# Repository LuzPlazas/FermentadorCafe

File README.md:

# FermentadorCafe
Códigos asociados al monitor de fermentación de café
-----------

DESARROLLO DE UN SISTEMA PARA EL MONITOREO INTELIGENTE DEL PROCESO DE FERMENTACIÓN DEL CAFÉ 

LUZ ADRIANA PLAZAS PEMBERTHY
CÓDIGO 2190651

UNIVERSIDAD AUTÓNOMA DE OCCIDENTE
2022

------------------------------
Código generado en el desarrollo de un sistema de monitoreo inteligente del proceso de fermentación del café para facilitarle al caficultor la producción de diferentes perfiles de café.

* Se encuentra el firmware para Arduino para la lectura y procesamiento de sensores.
* Se encuentra el software para Raspberry desarrollado en python para almacenamiento y análisis de datos.
* Se encuentran los códigos para entrenamiento de los modelos de aprendizaje automático y los dataset asociados en formato csv.

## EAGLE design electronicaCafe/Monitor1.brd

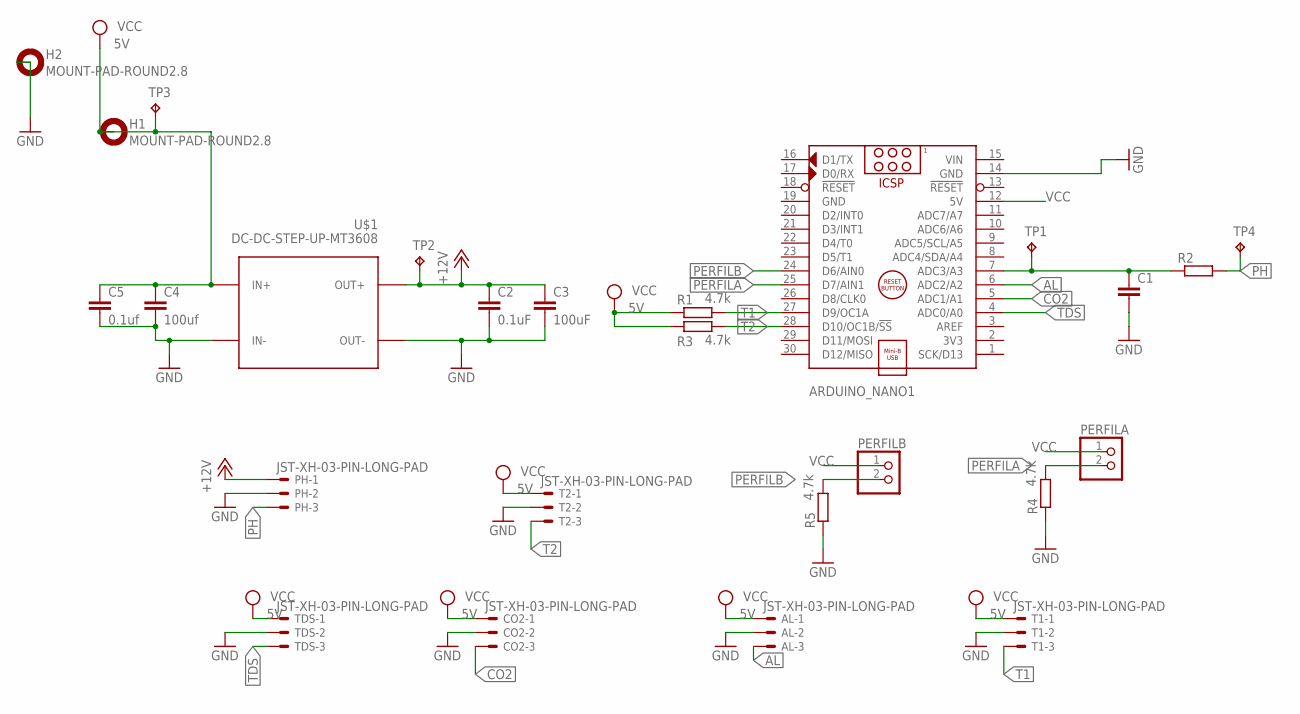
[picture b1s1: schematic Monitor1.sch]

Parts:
AL: JST-XH-03-PIN-LONG-PAD; JST-XH-03-PACKAGE-LONG-PAD
ARDUINO_NANO1: ARDUINO_NANO
C1: C-EU050-030X075; C050-030X075
C2: 0.1uF; C050-030X075
C3: 100uF; C050-045X075
C4: 100uf; C050-045X075
C5: 0.1uf; C050-030X075
CO2: JST-XH-03-PIN-LONG-PAD; JST-XH-03-PACKAGE-LONG-PAD
H1, H2: MOUNT-PAD-ROUND2.8; 2,8-PAD
PERFILA: PINHD-1X2; 1X02
PERFILB: PINHD-1X2; 1X02
PH: JST-XH-03-PIN-LONG-PAD; JST-XH-03-PACKAGE-LONG-PAD
R1, R3, R4, R5: 4.7k; 0309/10
R2: R-EU_0309/10; 0309/10
T1, T2: JST-XH-03-PIN-LONG-PAD; JST-XH-03-PACKAGE-LONG-PAD
TDS: JST-XH-03-PIN-LONG-PAD; JST-XH-03-PACKAGE-LONG-PAD
TP1, TP2, TP3, TP4: TPPAD1-13; P1-13
U$1: DC-DC-STEP-UP-MT3608

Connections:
+12V: C2.1, C3.1, PH.1, TP2.TP, U$1.OUT+
AL: AL.3, ARDUINO_NANO1.6 (ADC2/A2)
CO2: ARDUINO_NANO1.5 (ADC1/A1), CO2.3
GND: AL.2, ARDUINO_NANO1.14 (GND), ARDUINO_NANO1.19 (GND), C1.2, C2.2, C3.2, C4.2, C5.2, CO2.2, H2.B2,8, PH.2, R4.1, R5.1, T1.2, T2.2, TDS.2, U$1.IN-, U$1.OUT-
unnamed: ARDUINO_NANO1.7 (ADC3/A3), C1.1, R2.1, TP1.TP
PERFILA: ARDUINO_NANO1.25 (D7/AIN1), PERFILA.2, R4.2
PERFILB: ARDUINO_NANO1.24 (D6/AIN0), PERFILB.2, R5.2
PH: PH.3, R2.2, TP4.TP
T1: ARDUINO_NANO1.27 (D9/OC1A), R1.2, T1.3
T2: ARDUINO_NANO1.28 (D10/OC1B/!SS), R3.2, T2.3
TDS: ARDUINO_NANO1.4 (ADC0/A0), TDS.3
VCC: AL.1, ARDUINO_NANO1.12 (5V), C4.1, C5.1, CO2.1, H1.B2,8, PERFILA.1, PERFILB.1, R1.1, R3.1, T1.1, T2.1, TDS.1, TP3.TP, U$1.IN+
VIN: ARDUINO_NANO1.15 (VIN)

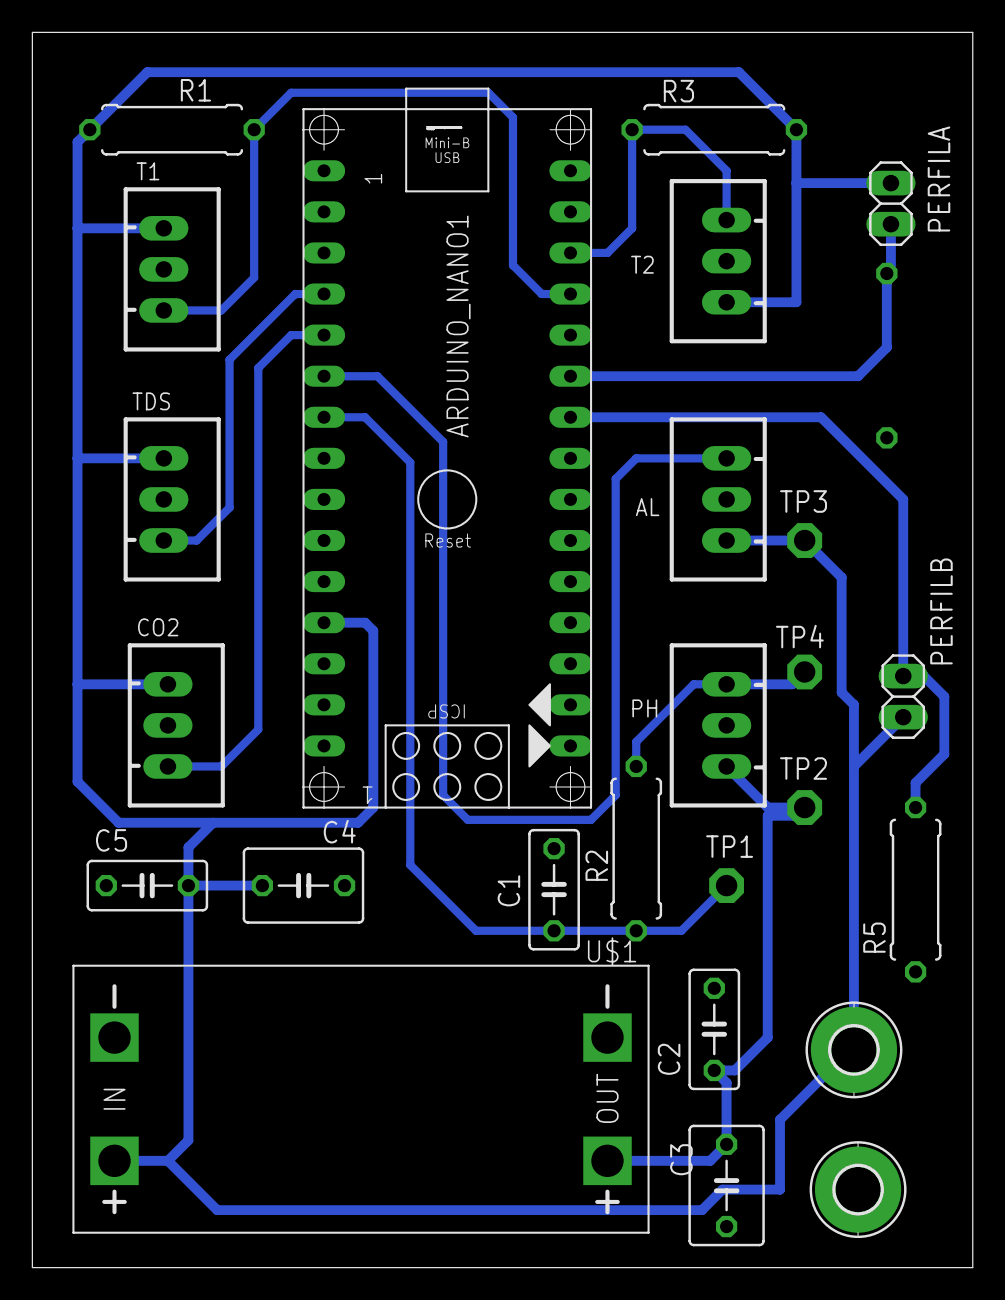
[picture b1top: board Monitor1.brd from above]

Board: 2 copper layers, 58.1 x 76.4 mm, 26 parts (1 on the bottom side), 12 nets.

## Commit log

2023-03-03 Archivos electrónicos
    Archivos de esquemático y PCB para programa EAGLE
2023-03-03 ARCHIVOS MECANICOS
    Archivos para diseño y fabricación mecánica, para software Solidworks.

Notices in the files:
parts and their libraries:
diy-modules: Released under the Creative Commons Attribution 4.0 International License: http://creativecommons.org/licenses/by/4.0
